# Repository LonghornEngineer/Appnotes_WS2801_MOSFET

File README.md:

***
###Appnotes_WS2801_MOSFET
***
**How to use the WS2801 LED PWM chip with MOSFETs to expand its current and voltage useage. **

The WS2801 is an interesting chip. It is a constant current LED driver with 3 drivers that the current can be set individually. This lends the WS2801 to be useful when driving RGB LEDs. Each channel runs off an internal 8-bit PWM (total 24-bits) that is serially clocked in over a 2-wire (data and clock) scheme. This gives each channel 256 levels of brightness. The WS2801 can also be chained together with other WS2801 chips to reduce I/O usage. 

See [here for more information](http://longhornengineer.com/category/appnotes/ws2801/).

***
**License Information**

This project is under the [Creative Commons Attribution-ShareAlike 4.0 International License](LICENSE.md). These files are provided with no warranty and should be used at your own risk. 

***

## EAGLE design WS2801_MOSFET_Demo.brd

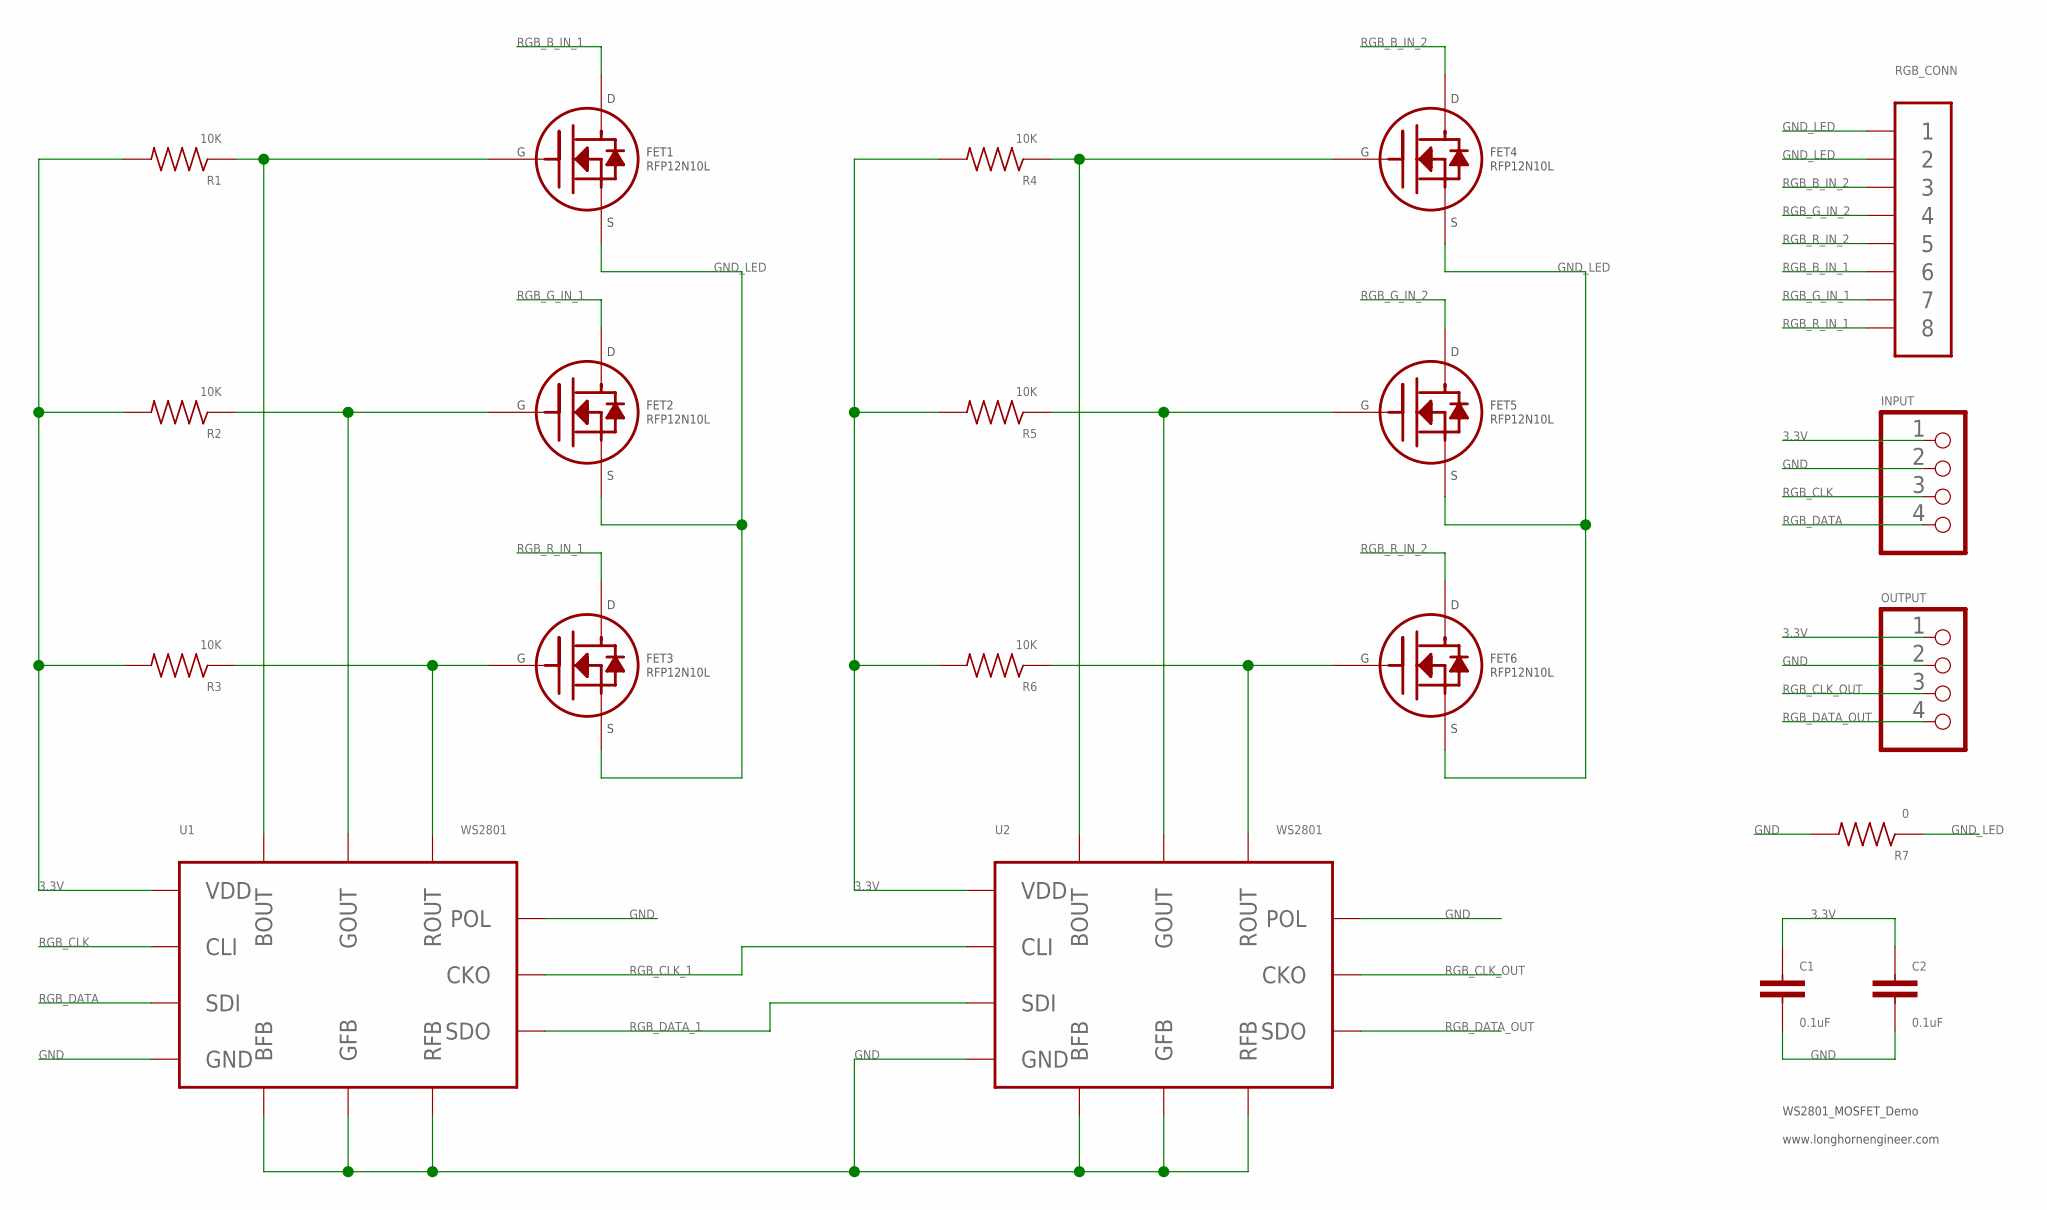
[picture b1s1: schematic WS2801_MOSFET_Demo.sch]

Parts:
C1, C2: 0.1uF; 0402
FET1, FET2, FET3, FET4, FET5, FET6: RFP12N10L; TO-220AB
INPUT: PH_1X04HEADER_PTH_ROUND; HEADER_01X04_PTH_ROUND
OUTPUT: PH_1X04HEADER_PTH_ROUND; HEADER_01X04_PTH_ROUND
R1, R2, R3, R4, R5, R6: 10K; 0805
R7: 0; 0402
RGB_CONN: 26-60-4080; HEADER_01X08_PTH_ROUND
U1, U2: WS2801; SOP-14

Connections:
3.3V: C1.1, C2.1, INPUT.1, OUTPUT.1, R1.2, R2.2, R3.2, R4.2, R5.2, R6.2, U1.14 (VDD), U2.14 (VDD)
GATE_B_IN_1: FET1.G (GATE), R1.1, U1.8 (BOUT)
GATE_B_IN_2: FET4.G (GATE), R4.1, U2.8 (BOUT)
GATE_G_IN_1: FET2.G (GATE), R2.1, U1.9 (GOUT)
GATE_G_IN_2: FET5.G (GATE), R5.1, U2.9 (GOUT)
GATE_R_IN_1: FET3.G (GATE), R3.1, U1.10 (ROUT)
GATE_R_IN_2: FET6.G (GATE), R6.1, U2.10 (ROUT)
GND: C1.2, C2.2, INPUT.2, OUTPUT.2, R7.2, U1.3 (POL), U1.4 (RFB), U1.5 (GFB), U1.6 (BFB), U1.7 (GND), U2.3 (POL), U2.4 (RFB), U2.5 (GFB), U2.6 (BFB), U2.7 (GND)
GND_LED: FET1.S (SOURCE), FET2.S (SOURCE), FET3.S (SOURCE), FET4.S (SOURCE), FET5.S (SOURCE), FET6.S (SOURCE), R7.1, RGB_CONN.1, RGB_CONN.2
RGB_B_IN_1: FET1.D (DRAIN), RGB_CONN.6
RGB_B_IN_2: FET4.D (DRAIN), RGB_CONN.3
RGB_CLK: INPUT.3, U1.1 (CLI)
RGB_CLK_1: U1.13 (CKO), U2.1 (CLI)
RGB_CLK_OUT: OUTPUT.3, U2.13 (CKO)
RGB_DATA: INPUT.4, U1.2 (SDI)
RGB_DATA_1: U1.12 (SDO), U2.2 (SDI)
RGB_DATA_OUT: OUTPUT.4, U2.12 (SDO)
RGB_G_IN_1: FET2.D (DRAIN), RGB_CONN.7
RGB_G_IN_2: FET5.D (DRAIN), RGB_CONN.4
RGB_R_IN_1: FET3.D (DRAIN), RGB_CONN.8
RGB_R_IN_2: FET6.D (DRAIN), RGB_CONN.5

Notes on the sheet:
WS2801_MOSFET_Demo
www.longhornengineer.com

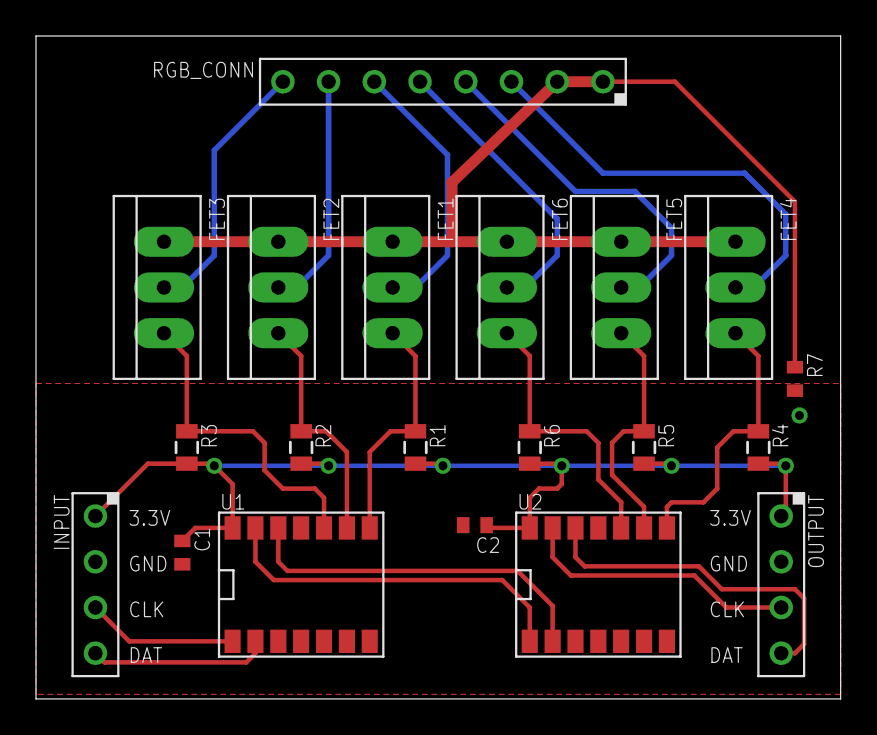
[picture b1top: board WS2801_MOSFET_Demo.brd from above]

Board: 2 copper layers, 44.7 x 36.8 mm, 20 parts (0 on the bottom side), 21 nets.

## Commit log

2013-12-19 Push WS2801 Datasheet.
2013-12-19 Added the Eagle files and Layout images.
2013-12-26 Added cascade LEDs and formulas.
2014-04-09 Updating License to CC-BY-SA
2014-04-09 Update to CC-BY-SA License.
2016-08-23 Updating Readme and banner information.
